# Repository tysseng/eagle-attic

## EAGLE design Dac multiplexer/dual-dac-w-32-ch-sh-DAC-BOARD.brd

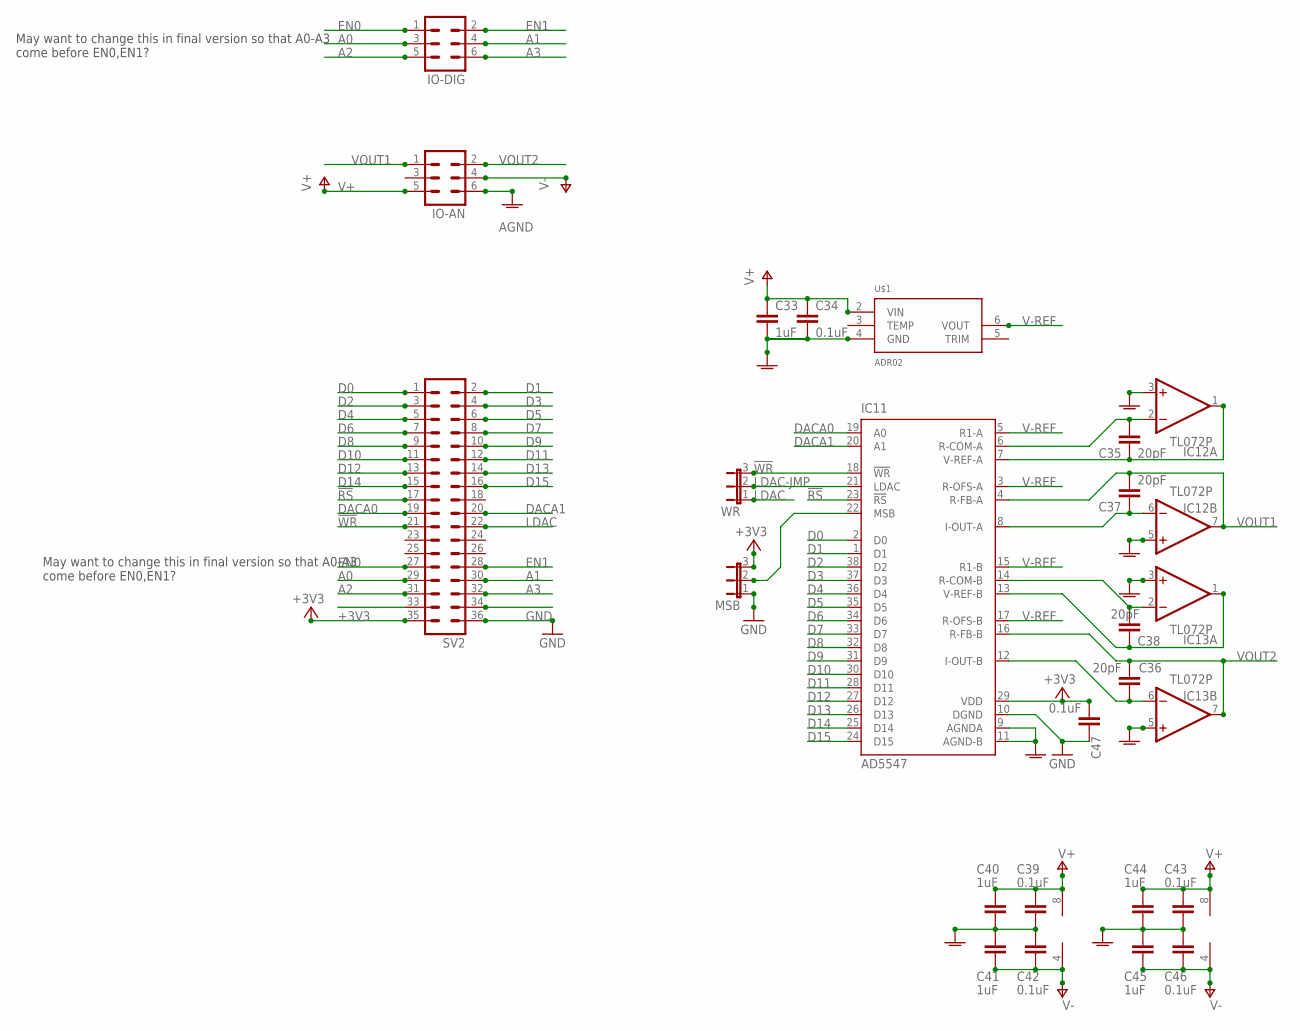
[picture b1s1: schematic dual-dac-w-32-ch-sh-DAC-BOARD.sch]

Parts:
C33, C40, C41, C44, C45: 1uF; C0603
C34, C39, C42, C43, C46, C47: 0.1uF; C0603
C35, C36, C37, C38: 20pF; C0603
IC11: AD5547; TSSOP38
IC12, IC13: TL072P; DIL08
IO-AN: MA03-2
IO-DIG: MA03-2
MSB: JP2E; JP2
SV2: MA18-2
U$1: ADR02; SO08
WR: JP2E; JP2

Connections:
!RS: IC11.23 (!RS), SV2.17
!WR: IC11.18 (!WR), SV2.21, WR.3
+3V3: C47.1, IC11.29 (VDD), MSB.3, SV2.35
A0: IO-DIG.3, SV2.29
A1: IO-DIG.4, SV2.30
A2: IO-DIG.5, SV2.31
A3: IO-DIG.6, SV2.32
AGND: C33.2, C34.2, C39.1, C40.1, C41.2, C42.2, C43.1, C44.1, C45.2, C46.2, IC11.9 (AGNDA), IC11.11 (AGND-B), IC12.3 (+IN), IC12.5 (+IN), IC13.3 (+IN), IC13.5 (+IN), IO-AN.6, U$1.4 (GND)
D0: IC11.2 (D0), SV2.1
D1: IC11.1 (D1), SV2.2
D2: IC11.38 (D2), SV2.3
D3: IC11.37 (D3), SV2.4
D4: IC11.36 (D4), SV2.5
D5: IC11.35 (D5), SV2.6
D6: IC11.34 (D6), SV2.7
D7: IC11.33 (D7), SV2.8
D8: IC11.32 (D8), SV2.9
D9: IC11.31 (D9), SV2.10
D10: IC11.30 (D10), SV2.11
D11: IC11.28 (D11), SV2.12
D12: IC11.27 (D12), SV2.13
D13: IC11.26 (D13), SV2.14
D14: IC11.25 (D14), SV2.15
D15: IC11.24 (D15), SV2.16
DACA0: IC11.19 (A0), SV2.19
DACA1: IC11.20 (A1), SV2.20
EN0: IO-DIG.1, SV2.27
EN1: IO-DIG.2, SV2.28
GND: C47.2, IC11.10 (DGND), MSB.1, SV2.36
LDAC: SV2.22, WR.1
LDAC-JMP: IC11.21 (LDAC), WR.2
unnamed: C35.2, IC11.6 (R-COM-A), IC12.2 (-IN)
unnamed: C35.1, IC11.7 (V-REF-A), IC12.1 (OUT)
unnamed: C38.2, IC11.14 (R-COM-B), IC13.2 (-IN)
unnamed: C38.1, IC11.13 (V-REF-B), IC13.1 (OUT)
unnamed: IC11.22 (MSB), MSB.2
unnamed: C36.2, IC11.12 (I-OUT-B), IC13.6 (-IN)
unnamed: C37.2, IC11.8 (I-OUT-A), IC12.6 (-IN)
V+: C33.1, C34.1, C39.2, C40.2, C43.2, C44.2, IC12.8 (V+), IC13.8 (V+), IO-AN.5, U$1.2 (VIN)
V-: C41.1, C42.1, C45.1, C46.1, IC12.4 (V-), IC13.4 (V-), IO-AN.4
V-REF: IC11.3 (R-OFS-A), IC11.5 (R1-A), IC11.15 (R1-B), IC11.17 (R-OFS-B), U$1.6 (VOUT)
VOUT1: C37.1, IC11.4 (R-FB-A), IC12.7 (OUT), IO-AN.1
VOUT2: C36.1, IC11.16 (R-FB-B), IC13.7 (OUT), IO-AN.2

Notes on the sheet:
May want to change this in final version so that A0-A3 come before EN0,EN1?

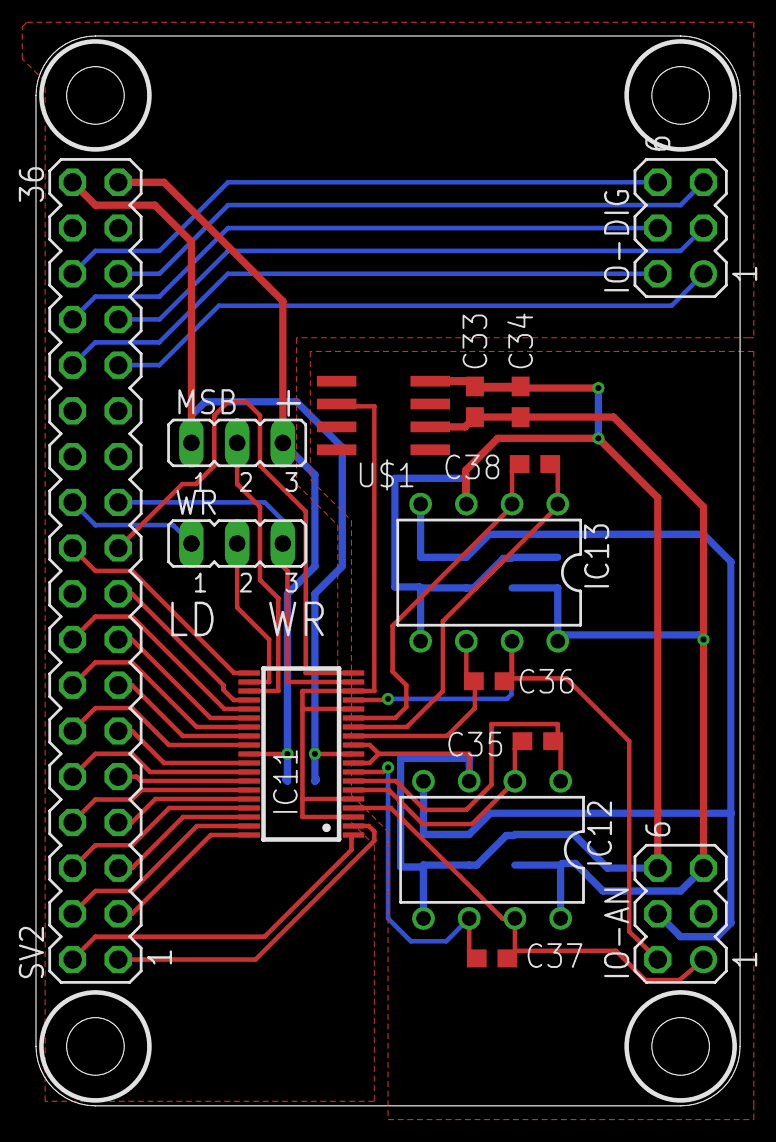
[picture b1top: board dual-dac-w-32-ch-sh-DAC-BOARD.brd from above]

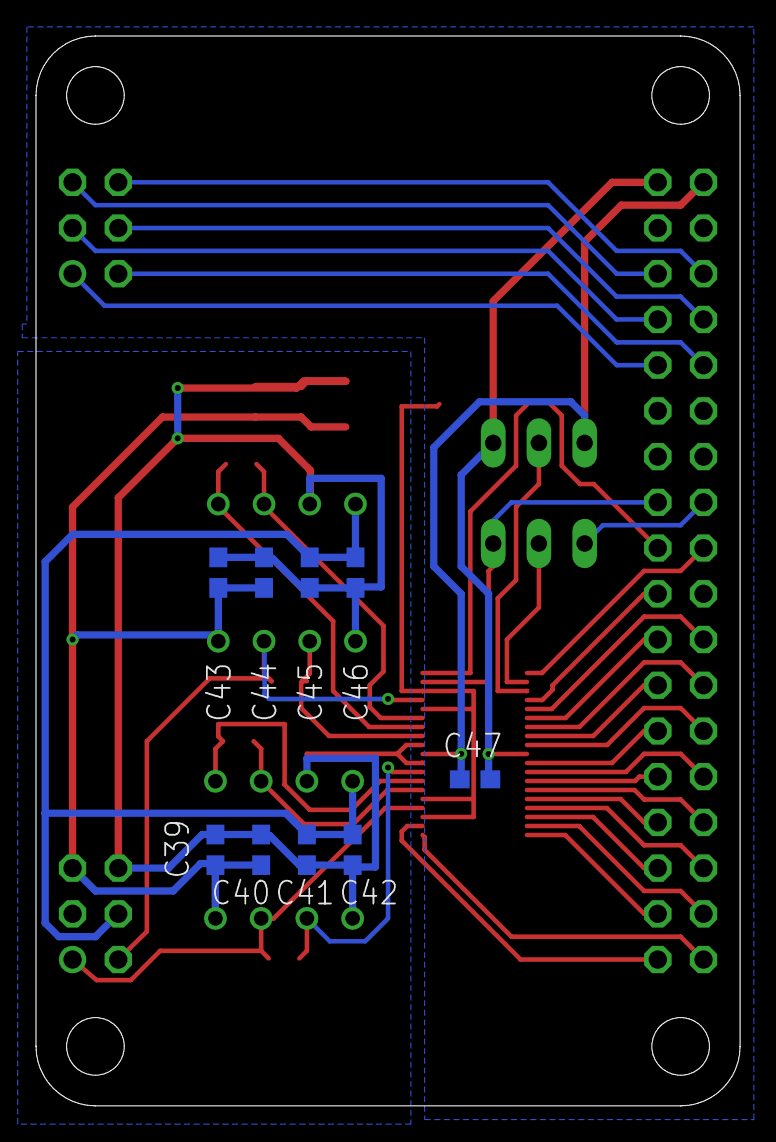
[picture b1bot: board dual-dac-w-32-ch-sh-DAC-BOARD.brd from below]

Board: 2 copper layers, 39.1 x 59.4 mm, 24 parts (9 on the bottom side), 43 nets.

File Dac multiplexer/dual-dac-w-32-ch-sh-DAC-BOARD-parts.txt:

Partlist

Exported from dual-dac-w-32-ch-sh-DAC-BOARD.sch at 01.03.2015 13:25:53

EAGLE Version 7.2.0 Copyright (c) 1988-2014 CadSoft

Assembly variant: 

Part     Value          Device     Package  Library  Sheet


C34      0.1uF          C-EUC0603  C0603    resistor 1
C39      0.1uF          C-EUC0603  C0603    resistor 1
C42      0.1uF          C-EUC0603  C0603    resistor 1
C43      0.1uF          C-EUC0603  C0603    resistor 1
C46      0.1uF          C-EUC0603  C0603    resistor 1
C47      0.1uF          C-EUC0603  C0603    resistor 1

C35      20pF           C-EUC0603  C0603    resistor 1
C36      20pF           C-EUC0603  C0603    resistor 1
C37      20pF           C-EUC0603  C0603    resistor 1
C38      20pF           C-EUC0603  C0603    resistor 1

C33      1uF            C-EUC0603  C0603    resistor 1
C40      1uF            C-EUC0603  C0603    resistor 1
C41      1uF            C-EUC0603  C0603    resistor 1
C44      1uF            C-EUC0603  C0603    resistor 1
C45      1uF            C-EUC0603  C0603    resistor 1

IC11     AD5547         AD5547     TSSOP38  joakim   1

IC12     TL072P         TL072P     DIL08    linear   1
IC13     TL072P         TL072P     DIL08    linear   1
IO-AN                   MA03-2     MA03-2   con-lstb 1
IO-DIG                  MA03-2     MA03-2   con-lstb 1
MSB                     JP2E       JP2      jumper   1
SV2                     MA18-2     MA18-2   con-lstb 1
U$1      ADR02          ADR02      SO08     joakim   1
WR                      JP2E       JP2      jumper   1

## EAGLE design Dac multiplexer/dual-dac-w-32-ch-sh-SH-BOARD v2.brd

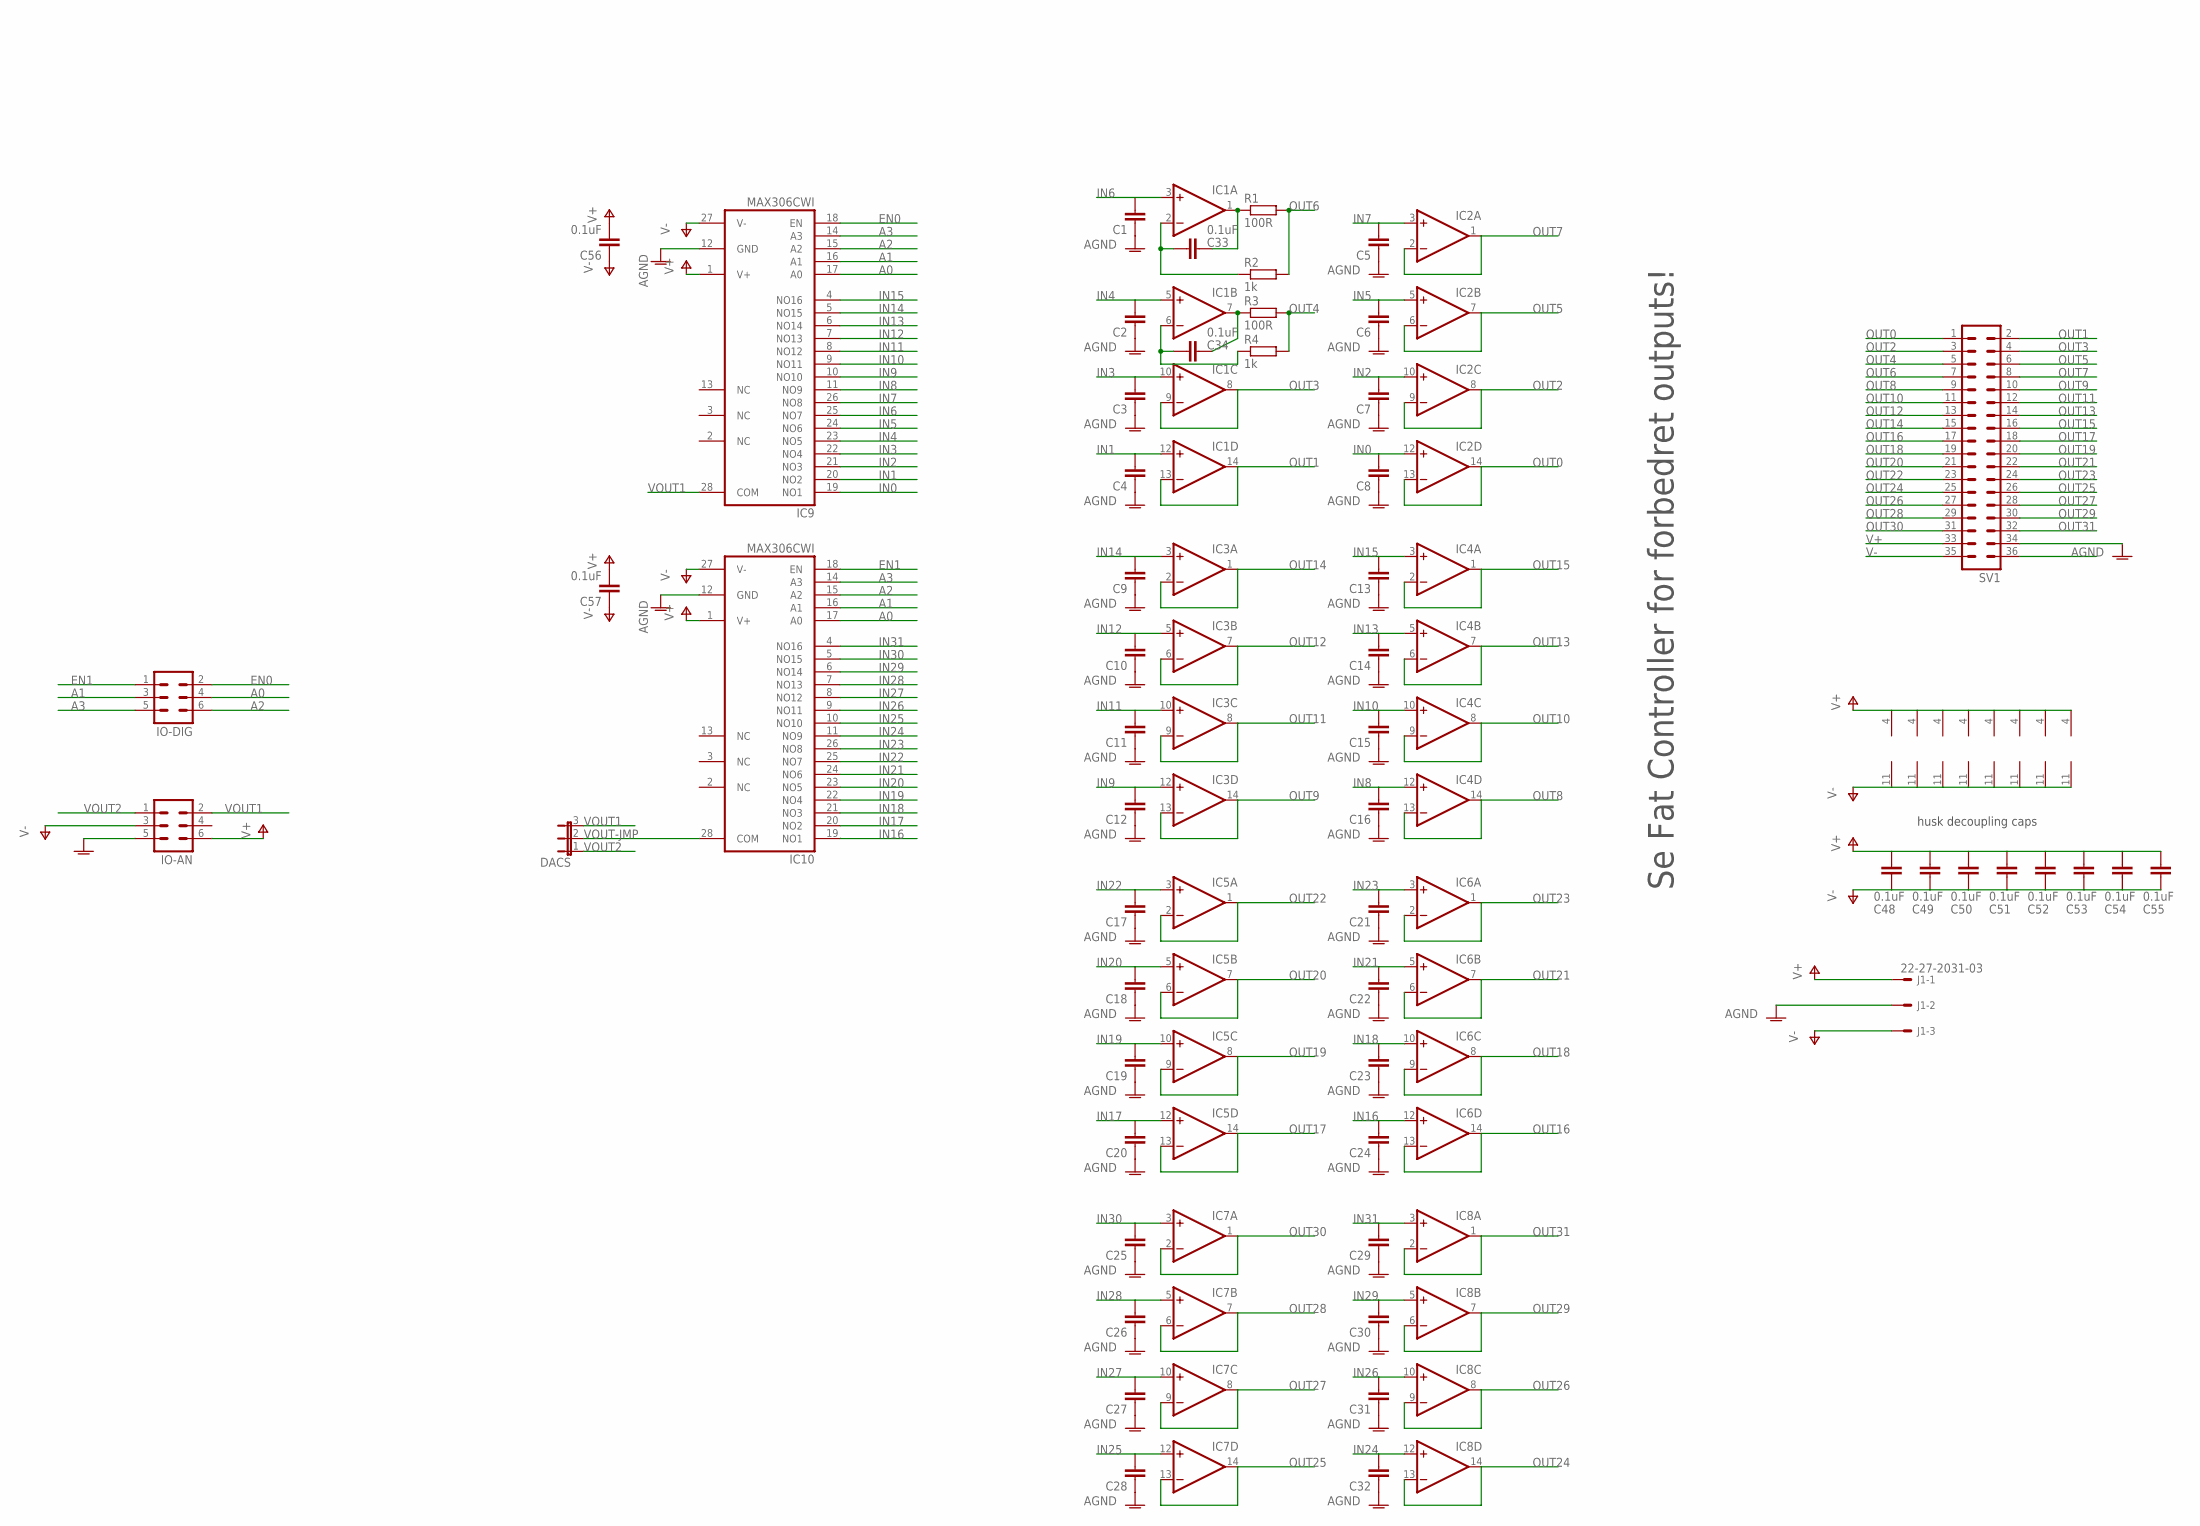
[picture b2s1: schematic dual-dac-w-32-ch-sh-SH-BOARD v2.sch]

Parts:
C1, C2, C3, C4, C5, C6, C7, C8, C9, C10, C11, C12, C13, C14, C15, C16, C17, C18, C19, C20, C21, C22, C23, C24, C25, C26, C27, C28, C29, C30, C31, C32: C-EUC1206; C1206
C33, C34, C48, C49, C50, C51, C52, C53, C54, C55, C56, C57: 0.1uF; C0603
DACS: JP2E; JP2
IC1, IC2, IC3, IC4, IC5, IC6, IC7, IC8: TL074D; SO14
IC9, IC10: MAX306CWI; SO28L
IO-AN: MA03-2
IO-DIG: MA03-2
J1: 22-27-2031-03; 6410-03
R1, R3: 100R; R0603
R2, R4: 1k; R0603
SV1: MA18-2

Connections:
A0: IC9.17 (A0), IC10.17 (A0), IO-DIG.4
A1: IC9.16 (A1), IC10.16 (A1), IO-DIG.3
A2: IC9.15 (A2), IC10.15 (A2), IO-DIG.6
A3: IC9.14 (A3), IC10.14 (A3), IO-DIG.5
AGND: C1.1, C2.1, C3.1, C4.1, C5.1, C6.1, C7.1, C8.1, C9.1, C10.1, C11.1, C12.1, C13.1, C14.1, C15.1, C16.1, C17.1, C18.1, C19.1, C20.1, C21.1, C22.1, C23.1, C24.1, C25.1, C26.1, C27.1, C28.1, C29.1, C30.1, C31.1, C32.1, IC9.12 (GND), IC10.12 (GND), IO-AN.5, J1.2, SV1.34
EN0: IC9.18 (EN), IO-DIG.2
EN1: IC10.18 (EN), IO-DIG.1
IN0: C8.2, IC2.12 (+IN), IC9.19 (NO1)
IN1: C4.2, IC1.12 (+IN), IC9.20 (NO2)
IN2: C7.2, IC2.10 (+IN), IC9.21 (NO3)
IN3: C3.2, IC1.10 (+IN), IC9.22 (NO4)
IN4: C2.2, IC1.5 (+IN), IC9.23 (NO5)
IN5: C6.2, IC2.5 (+IN), IC9.24 (NO6)
IN6: C1.2, IC1.3 (+IN), IC9.25 (NO7)
IN7: C5.2, IC2.3 (+IN), IC9.26 (NO8)
IN8: C16.2, IC4.12 (+IN), IC9.11 (NO9)
IN9: C12.2, IC3.12 (+IN), IC9.10 (NO10)
IN10: C15.2, IC4.10 (+IN), IC9.9 (NO11)
IN11: C11.2, IC3.10 (+IN), IC9.8 (NO12)
IN12: C10.2, IC3.5 (+IN), IC9.7 (NO13)
IN13: C14.2, IC4.5 (+IN), IC9.6 (NO14)
IN14: C9.2, IC3.3 (+IN), IC9.5 (NO15)
IN15: C13.2, IC4.3 (+IN), IC9.4 (NO16)
IN16: C24.2, IC6.12 (+IN), IC10.19 (NO1)
IN17: C20.2, IC5.12 (+IN), IC10.20 (NO2)
IN18: C23.2, IC6.10 (+IN), IC10.21 (NO3)
IN19: C19.2, IC5.10 (+IN), IC10.22 (NO4)
IN20: C18.2, IC5.5 (+IN), IC10.23 (NO5)
IN21: C22.2, IC6.5 (+IN), IC10.24 (NO6)
IN22: C17.2, IC5.3 (+IN), IC10.25 (NO7)
IN23: C21.2, IC6.3 (+IN), IC10.26 (NO8)
IN24: C32.2, IC8.12 (+IN), IC10.11 (NO9)
IN25: C28.2, IC7.12 (+IN), IC10.10 (NO10)
IN26: C31.2, IC8.10 (+IN), IC10.9 (NO11)
IN27: C27.2, IC7.10 (+IN), IC10.8 (NO12)
IN28: C26.2, IC7.5 (+IN), IC10.7 (NO13)
IN29: C30.2, IC8.5 (+IN), IC10.6 (NO14)
IN30: C25.2, IC7.3 (+IN), IC10.5 (NO15)
IN31: C29.2, IC8.3 (+IN), IC10.4 (NO16)
unnamed: C33.2, IC1.2 (-IN), R2.1
unnamed: C33.1, IC1.1 (OUT), R1.1
unnamed: C34.1, IC1.7 (OUT), R3.1
unnamed: C34.2, IC1.6 (-IN), R4.1
OUT0: IC2.13 (-IN), IC2.14 (OUT), SV1.1
OUT1: IC1.13 (-IN), IC1.14 (OUT), SV1.2
OUT2: IC2.8 (OUT), IC2.9 (-IN), SV1.3
OUT3: IC1.8 (OUT), IC1.9 (-IN), SV1.4
OUT4: R3.2, R4.2, SV1.5
OUT5: IC2.6 (-IN), IC2.7 (OUT), SV1.6
OUT6: R1.2, R2.2, SV1.7
OUT7: IC2.1 (OUT), IC2.2 (-IN), SV1.8
OUT8: IC4.13 (-IN), IC4.14 (OUT), SV1.9
OUT9: IC3.13 (-IN), IC3.14 (OUT), SV1.10
OUT10: IC4.8 (OUT), IC4.9 (-IN), SV1.11
OUT11: IC3.8 (OUT), IC3.9 (-IN), SV1.12
OUT12: IC3.6 (-IN), IC3.7 (OUT), SV1.13
OUT13: IC4.6 (-IN), IC4.7 (OUT), SV1.14
OUT14: IC3.1 (OUT), IC3.2 (-IN), SV1.15
OUT15: IC4.1 (OUT), IC4.2 (-IN), SV1.16
OUT16: IC6.13 (-IN), IC6.14 (OUT), SV1.17
OUT17: IC5.13 (-IN), IC5.14 (OUT), SV1.18
OUT18: IC6.8 (OUT), IC6.9 (-IN), SV1.19
OUT19: IC5.8 (OUT), IC5.9 (-IN), SV1.20
OUT20: IC5.6 (-IN), IC5.7 (OUT), SV1.21
OUT21: IC6.6 (-IN), IC6.7 (OUT), SV1.22
OUT22: IC5.1 (OUT), IC5.2 (-IN), SV1.23
OUT23: IC6.1 (OUT), IC6.2 (-IN), SV1.24
OUT24: IC8.13 (-IN), IC8.14 (OUT), SV1.25
OUT25: IC7.13 (-IN), IC7.14 (OUT), SV1.26
OUT26: IC8.8 (OUT), IC8.9 (-IN), SV1.27
OUT27: IC7.8 (OUT), IC7.9 (-IN), SV1.28
OUT28: IC7.6 (-IN), IC7.7 (OUT), SV1.29
OUT29: IC8.6 (-IN), IC8.7 (OUT), SV1.30
OUT30: IC7.1 (OUT), IC7.2 (-IN), SV1.31
OUT31: IC8.1 (OUT), IC8.2 (-IN), SV1.32
V+: C48.2, C49.2, C50.2, C51.2, C52.2, C53.2, C54.2, C55.2, C56.2, C57.2, IC1.4 (V+), IC2.4 (V+), IC3.4 (V+), IC4.4 (V+), IC5.4 (V+), IC6.4 (V+), IC7.4 (V+), IC8.4 (V+), IC9.1 (V+), IC10.1 (V+), IO-AN.6, J1.1, SV1.33
V-: C48.1, C49.1, C50.1, C51.1, C52.1, C53.1, C54.1, C55.1, C56.1, C57.1, IC1.11 (V-), IC2.11 (V-), IC3.11 (V-), IC4.11 (V-), IC5.11 (V-), IC6.11 (V-), IC7.11 (V-), IC8.11 (V-), IC9.27 (V-), IC10.27 (V-), IO-AN.3, J1.3, SV1.35
VOUT1: DACS.3, IC9.28 (COM), IO-AN.2
VOUT2: DACS.1, IO-AN.1
VOUT-JMP: DACS.2, IC10.28 (COM)

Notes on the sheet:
husk decoupling caps
Se Fat Controller for forbedret outputs!

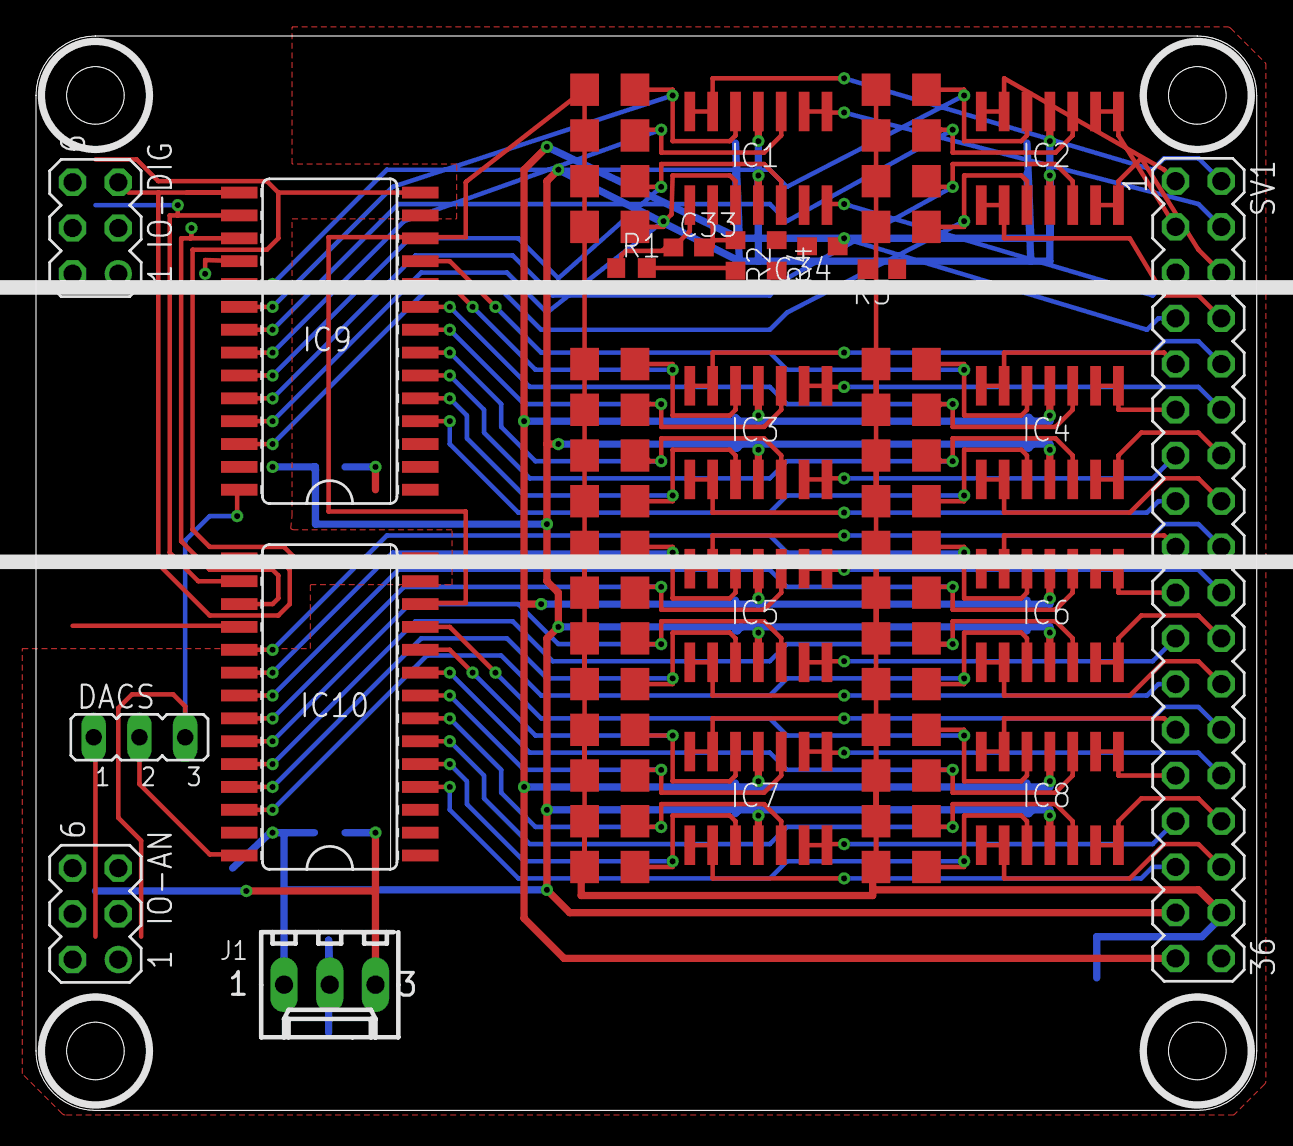
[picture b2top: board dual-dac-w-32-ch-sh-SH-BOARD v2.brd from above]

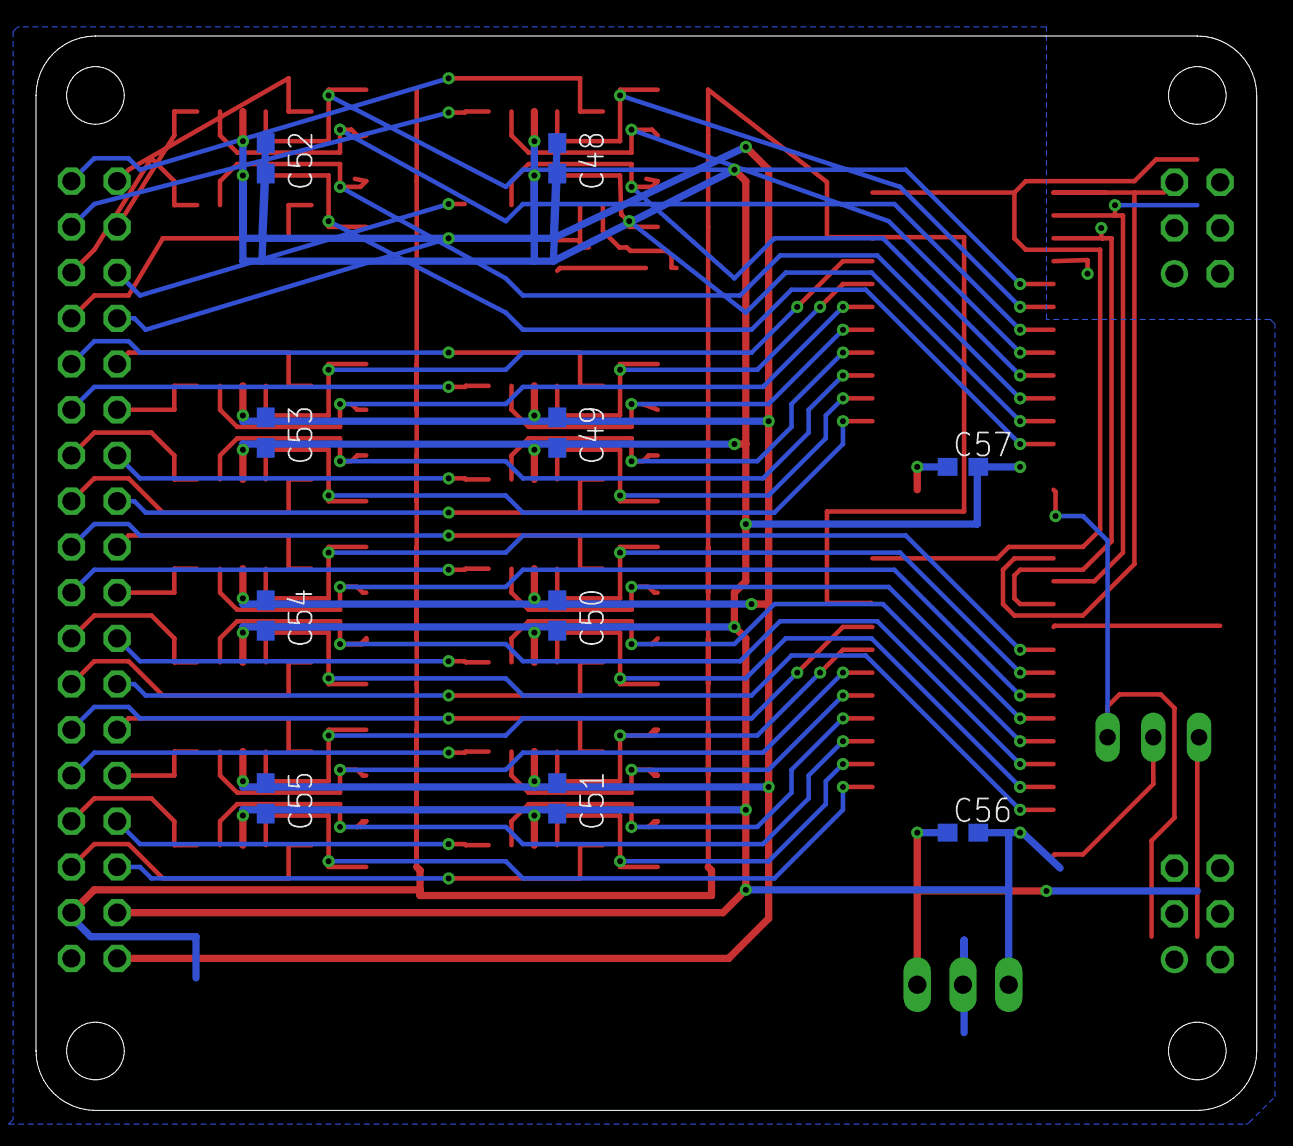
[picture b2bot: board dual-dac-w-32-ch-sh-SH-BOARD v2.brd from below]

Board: 2 copper layers, 67.8 x 59.7 mm, 63 parts (10 on the bottom side), 80 nets.

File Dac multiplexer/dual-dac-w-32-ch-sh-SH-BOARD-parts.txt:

Partlist

Exported from dual-dac-w-32-ch-sh-SH-BOARD.sch at 01.03.2015 13:32:01

EAGLE Version 7.2.0 Copyright (c) 1988-2014 CadSoft

Assembly variant: 

Part     Value          Device        Package  Library   Sheet

C1                      C-EUC1206     C1206    resistor  1
C2                      C-EUC1206     C1206    resistor  1
C3                      C-EUC1206     C1206    resistor  1
C4                      C-EUC1206     C1206    resistor  1
C5                      C-EUC1206     C1206    resistor  1
C6                      C-EUC1206     C1206    resistor  1
C7                      C-EUC1206     C1206    resistor  1
C8                      C-EUC1206     C1206    resistor  1
C9                      C-EUC1206     C1206    resistor  1
C10                     C-EUC1206     C1206    resistor  1
C11                     C-EUC1206     C1206    resistor  1
C12                     C-EUC1206     C1206    resistor  1
C13                     C-EUC1206     C1206    resistor  1
C14                     C-EUC1206     C1206    resistor  1
C15                     C-EUC1206     C1206    resistor  1
C16                     C-EUC1206     C1206    resistor  1
C17                     C-EUC1206     C1206    resistor  1
C18                     C-EUC1206     C1206    resistor  1
C19                     C-EUC1206     C1206    resistor  1
C20                     C-EUC1206     C1206    resistor  1
C21                     C-EUC1206     C1206    resistor  1
C22                     C-EUC1206     C1206    resistor  1
C23                     C-EUC1206     C1206    resistor  1
C24                     C-EUC1206     C1206    resistor  1
C25                     C-EUC1206     C1206    resistor  1
C26                     C-EUC1206     C1206    resistor  1
C27                     C-EUC1206     C1206    resistor  1
C28                     C-EUC1206     C1206    resistor  1
C29                     C-EUC1206     C1206    resistor  1
C30                     C-EUC1206     C1206    resistor  1
C31                     C-EUC1206     C1206    resistor  1
C32                     C-EUC1206     C1206    resistor  1

C48      0.1uF          C-EUC0603     C0603    resistor  1
C49      0.1uF          C-EUC0603     C0603    resistor  1
C50      0.1uF          C-EUC0603     C0603    resistor  1
C51      0.1uF          C-EUC0603     C0603    resistor  1
C52      0.1uF          C-EUC0603     C0603    resistor  1
C53      0.1uF          C-EUC0603     C0603    resistor  1
C54      0.1uF          C-EUC0603     C0603    resistor  1
C55      0.1uF          C-EUC0603     C0603    resistor  1
C56      0.1uF          C-EUC0603     C0603    resistor  1
C57      0.1uF          C-EUC0603     C0603    resistor  1

DACS                    JP2E          JP2      jumper    1
IC1      TL074D         TL074D        SO14     linear    1
IC2      TL074D         TL074D        SO14     linear    1
IC3      TL074D         TL074D        SO14     linear    1
IC4      TL074D         TL074D        SO14     linear    1
IC5      TL074D         TL074D        SO14     linear    1
IC6      TL074D         TL074D        SO14     linear    1
IC7      TL074D         TL074D        SO14     linear    1
IC8      TL074D         TL074D        SO14     linear    1

IC9      MAX306CWI      MAX306CWI     SO28L    maxim     1
IC10     MAX306CWI      MAX306CWI     SO28L    maxim     1
IO-AN                   MA03-2        MA03-2   con-lstb  1
IO-DIG                  MA03-2        MA03-2   con-lstb  1
J1       22-27-2031-03  22-27-2031-03 6410-03  con-molex 1
SV1                     MA18-2        MA18-2   con-lstb  1

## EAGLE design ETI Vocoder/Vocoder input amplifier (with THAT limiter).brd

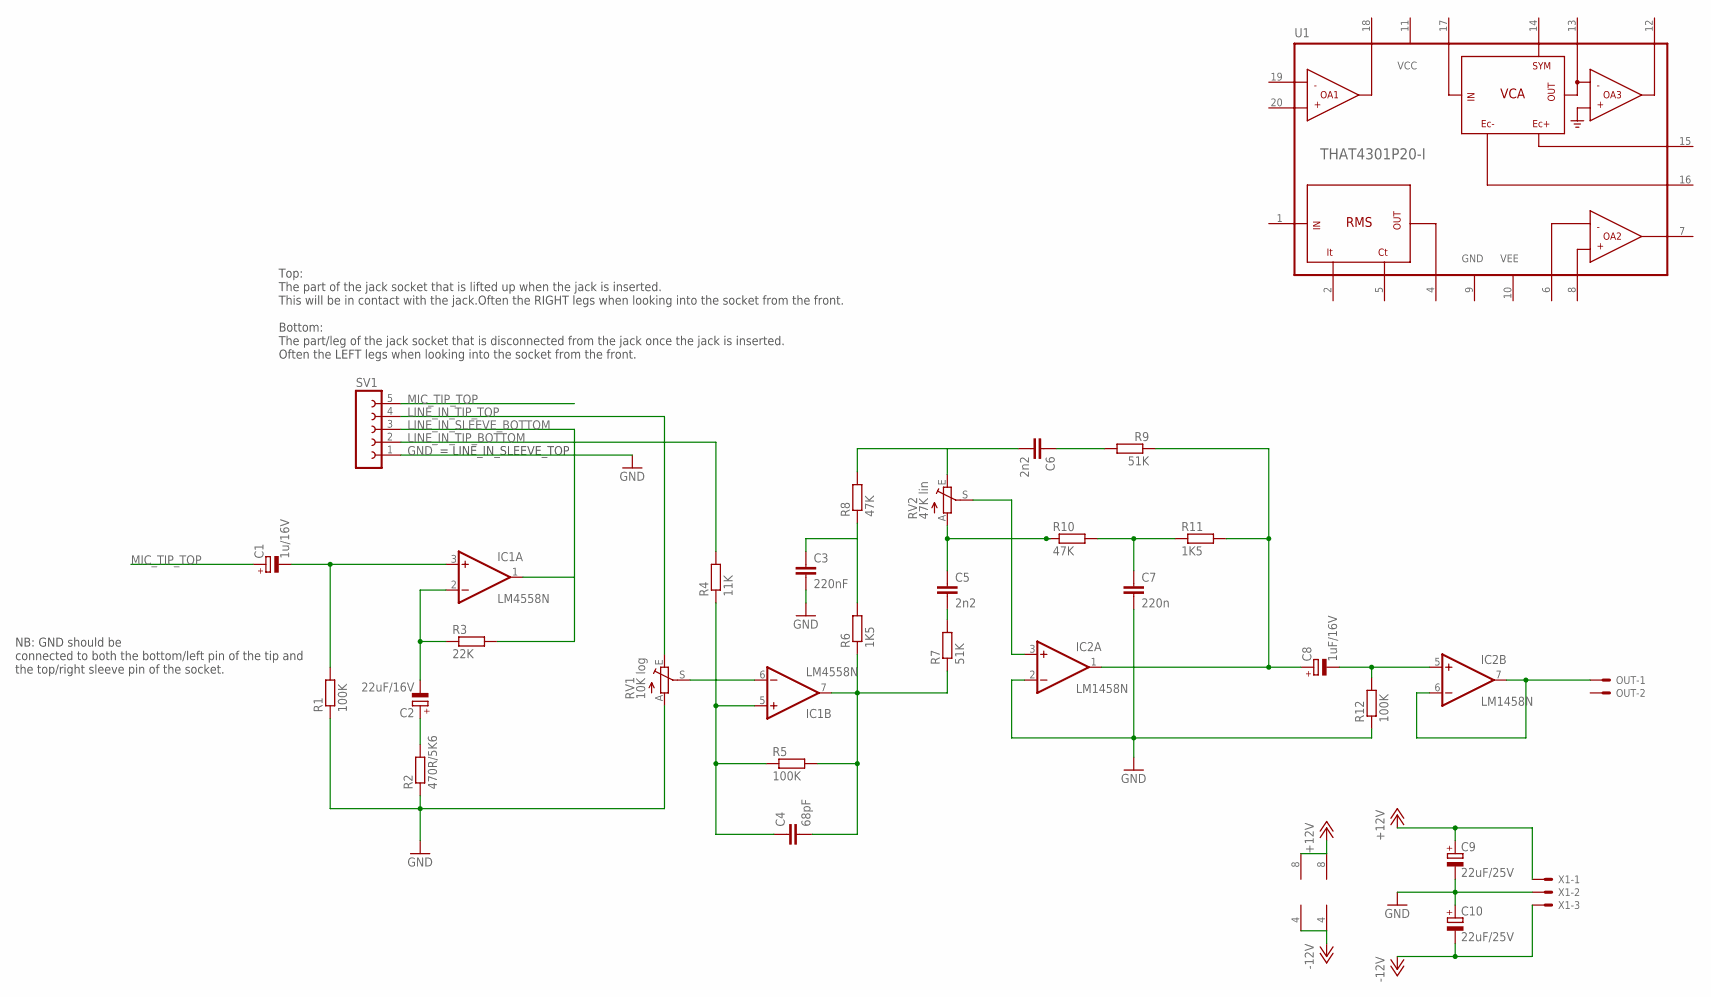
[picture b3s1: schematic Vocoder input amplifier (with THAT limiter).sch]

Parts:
C1: 1u/16V; E2,5-5
C2: 22uF/16V; E2,5-5
C3: 220nF; C050-030X075
C4: 68pF; C025-025X050
C5, C6: 2n2; C050-030X075
C7: 220n; C050-030X075
C8: 1uF/16V; E2,5-5
C9, C10: 22uF/25V; E2,5-5
IC1: LM4558N; DIL08
IC2: LM1458N; DIL08
OUT: 22-23-2021
R1, R5, R12: 100K; 0207/7
R2: 470R/5K6; 0207/7
R3: 22K; 0207/7
R4: 11K; 0207/7
R6, R11: 1K5; 0207/7
R7, R9: 51K; 0207/7
R8, R10: 47K; 0207/7
RV1: 10K log; CIP20C-6MM
RV2: 47K lin; CIP20C-6MM
SV1: FE05-1
U1: THAT4301P20-I; DIL20
X1: KK-156-3

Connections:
+12V: C9.+, IC1.8 (V+), IC2.8 (V+), X1.1
-12V: C10.-, IC1.4 (V-), IC2.4 (V-), X1.3
GND: C3.2, C7.2, C9.-, C10.+, IC2.2 (-IN), R1.1, R2.1, R12.1, RV1.A, SV1.1, U1.9 (GND), X1.2
LINE_IN_SLEEVE_BOTTOM: R4.2, SV1.2
LINE_IN_TIP_BOTTOM: IC1.1 (OUT), R3.2, SV1.3
LINE_IN_TIP_TOP: RV1.E, SV1.4
MIC_TIP_TOP: C1.+, SV1.5
unnamed: C2.-, IC1.2 (-IN), R3.1
unnamed: C1.-, IC1.3 (+IN), R1.2
unnamed: C2.+, R2.2
unnamed: C3.1, R6.2, R8.1
unnamed: C4.1, IC1.5 (+IN), R4.1, R5.1
unnamed: IC1.6 (-IN), RV1.S
unnamed: C4.2, IC1.7 (OUT), R5.2, R6.1, R7.1
unnamed: C5.2, R7.2
unnamed: C6.2, R8.2, RV2.E
unnamed: IC2.3 (+IN), RV2.S
unnamed: C5.1, R10.1, RV2.A
unnamed: C7.1, R10.2, R11.1
unnamed: C8.-, IC2.5 (+IN), R12.2
unnamed: C6.1, R9.2
unnamed: C8.+, IC2.1 (OUT), R9.1, R11.2
unnamed: IC2.6 (-IN), IC2.7 (OUT), OUT.1
VCC: U1.11 (VCC)
VEE: U1.10 (VEE)

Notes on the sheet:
Top: The part of the jack socket that is lifted up when the jack is inserted. This will be in contact with the jack.Often the RIGHT legs when looking into the socket from the front. Bottom: The part/leg of the jack socket that is disconnected from the jack once the jack is inserted. Often the LEFT 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
= LINE_IN_SLEEVE_TOP
NB: GND should be connected to both the bottom/left pin of the tip and the top/right sleeve pin of the socket.

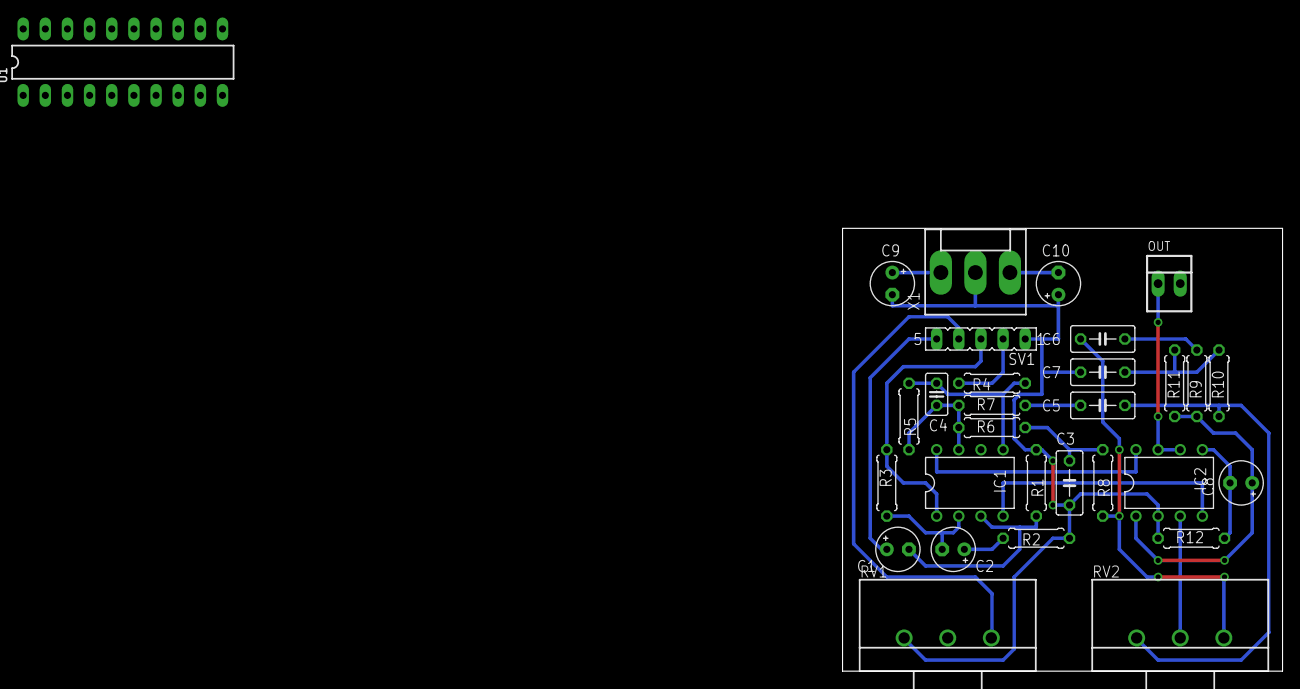
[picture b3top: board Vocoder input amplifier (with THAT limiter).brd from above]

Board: 2 copper layers, 50.5 x 50.8 mm, 30 parts (0 on the bottom side), 23 nets.

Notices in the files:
parts and their libraries:
that-corp-edit: Copyright (C) 2008-2010, Bob Starr
